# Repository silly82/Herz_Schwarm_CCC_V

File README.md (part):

# ❤️ CCC Heart Swarm Badge (Herz-Schwarm)

Synchronized ESP-NOW Heart Badges for the CCC Camp & Congress.
*Synchronisierte ESP-NOW Herz-Badges für das CCC Camp & den Congress.*

---

## Deutsch

### Was ist das?
Ein Schwarm von 8x8 LED Herz-Badges auf Basis der **Waveshare ESP32-S3-Matrix**. Die Badges kommunizieren über **ESP-NOW**, synchronisieren ihren Takt, reagieren auf die Nähe anderer Geräte (RSSI) und enthalten interaktive Easter Eggs.

### Funktionen
- **Herzschlag-Sync:** Alle Badges schlagen im exakt gleichen Rhythmus.
- **Näherungseffekt:** Je näher dir ein anderes Badge kommt, desto heller leuchtet dein Herz. Ab Badge-FW 1.6.0 zählt dafür das **nächste** Badge (stärkstes Signal), nicht mehr der Durchschnitt über alle; das Tempo hängt nicht mehr an der Nähe, damit alle im gleichen Takt bleiben. Ferngesteuerte Effekte leuchten auf allen Badges gleich hell (feste Helligkeit, `FX_BRIGHT`).
- **Primzahlen-Osterei:** Wenn die **Gesamtzahl im Schwarm** eine Primzahl ist — also **sichtbare andere Badges plus dein eigenes** (z. B. du + 12 andere = 13; nur unter 17, ab dort greift die Singularität) — pulsiert das Herz stärker und es gibt weisse Glitzer-Pixel.
- **Die Singularität (≥17 Geräte):** Sobald **mindestens 17 Geräte insgesamt** da sind (du + 16 sichtbare Peers), schaltet die Animation auf den **Regenbogen-Modus** um (nicht nur bei exakt 17).
- **Der Morse-Virus:** Morsese ein **«C»** (`- . - .`) über die BOOT-Taste, um einen weissen Blitz-Virus durch den gesamten Schwarm zu jagen. Ab Badge-FW 1.6.0 endet der Morse-Virus auf jedem Badge nach **3 s** von selbst (am Badge gibt es keine Stopp-Geste); nur der von Basisstation/App gestartete Virus läuft endlos bis zum Stopp.
- **Die Welle (Basisstation):** Eine Welle breitet sich von der Basisstation aus: Badges in der Nähe leuchten zuerst, weiter entfernte später. Ein Durchlauf dauert ~4 s und wiederholt sich ab Badge-FW 1.4.1 **endlos** (Zyklus alle 4000 ms) — beendet wird die Welle erst per **manuellem Stopp** (Modus `10`, oder `12` für alle Effekte): Toggle im Web-UI, MQTT-Payload `10` oder Nerves-Dashboard; Badges leiten den Stopp begrenzt weiter, so erreicht er auch Geräte außerhalb der Basis-Reichweite. Ältere Badges verstehen den Stopp nicht und laufen wie bisher nach ~4 s aus. Ab Badge-FW 1.4.0: Wer die Basis direkt hört, zündet nach deren Signal (−45 dBm → sofort, −95 dBm → 2 s); alle anderen nach dem Badge, von dem sie die Welle haben, plus 150–750 ms je nach Signal zu ihm. Jedes Badge rechnet dabei auf den gemeinsamen Wellenstart zurück und übernimmt den kürzesten bekannten Weg — die Welle läuft so auch zu Badges, die die Basis gar nicht hören.
- **Fernauslösung (Basisstation):** Kompatibles `SyncPacket` mit `mode` **1** (Virus), **2** (Regenbogen / Singularity-Optik), **3** (Primzahl-Party), **4** (Welle / RSSI-Ripple, 4-s-Zyklus), **5** (Beat-Puls ~150 ms), **6** (RSSI-Zonen-Farben), **7** (Ambient-Farbe), **8** (Strobe), **9** (Badge finden — nur das Badge mit der Ziel-MAC blinkt grün), **10** (Welle stoppen — beendet die laufende Welle, ab Badge-FW 1.4.1), **11** (Tap-Meldung — `virusID` = Tap-Zählerstand), **12** (Alle stoppen — global, `virusID` = Kennung des Stopps), **13** (Funk-Update auslösen — nur App + Bridge, ab Badge-FW 1.7.0). Ab Badge-FW **1.5.0** laufen alle visuellen Effekte **endlos**, bis man sie stoppt oder ein neu gestarteter visueller Effekt sie ersetzt („letzter Effekt gewinnt" — Beat und Identify bleiben dabei erhalten). Die früheren festen Fenster (Virus 3 s, Regenbogen 15 s, Primzahl 12 s, Zonen 5 s, Ambient 30 s, Strobe 2 s) sind nur noch **nominale Zykluslängen**, nach denen der Effekt sich wiederholt. Ausnahmen: **Beat** bleibt ein 150-ms-Puls pro Paket, **Identify** (Modus 9) bleibt 10 s. Neue `virusID` pro Effekt verhindert Doppel-Trigger; während eines Effekts wird der passende `mode` weitergesendet (Kettenreaktion im Schwarm).
- **Tap-Counter (BOOT-Taste, ab Badge-FW 1.5.0):** Kurze Drücke auf die BOOT-Taste (**≤ 250 ms** — dieselben Ereignisse, die in der Morse-Eingabe ein Punkt sind; Morse unverändert) werden gezählt und als Modus `11` gemeldet (`virusID` = Zählerstand, monoton; 3× im 60-ms-Abstand plus Nachsendung nach 1,2 s, einmal beim Start). Andere Badges leiten fremde Tap-Pakete begrenzt weiter (**23 Byte** mit angehängter Ursprungs-MAC) und merken sich je MAC den höchsten Stand (Dedup). Der Zählerstand wird gedrosselt in NVS gespeichert (Namespace `hstap`, max. 1 Schreibvorgang/30 s). In der Nerves-App endet die Kette als **Tap-Counter-Karte** (Gesamtsumme und je Badge, Reset mit Rückfrage — Reset setzt nur die Anzeige auf 0, die Badge-Zähler laufen weiter).
- **Alle stoppen (Modus `12`, ab Badge-FW 1.5.0):** Globaler Stopp. Ab Badge-FW 1.6.0 / Basisstation 0.4.2 / Bridge 0.4.2 / App 0.2.2 trägt jeder Stopp eine eigene Kennung im `virusID`-Feld und wirkt je Badge genau einmal — ein verspätetes Echo schaltet so keinen Effekt mehr ab, der nach dem Stopp gestartet wurde (`virusID = 0` von älteren Sendern wird weiter verstanden, dann ohne diesen Schutz). Badges deaktivieren alle Effekt-Slots außer Identify und leiten den Stopp begrenzt weiter (max. 3 Sendungen, ~60 ms Abstand, dann 1000 ms Sperre — gleiches Muster wie der Wellen-Stopp). Erreichbar über Dashboard-Knopf „Alle Effekte auf den Badges stoppen", Basisstation-Knopf „⏹ Alle stoppen", `POST /api/effect?m=12` oder MQTT-Payload `12`.
- **Bewegungssensor (ab Badge-FW 1.8.0):** Schütteln lässt das Herz 1,5 s mit weißen Funken flattern. Optional: „Herz immer aufrecht" und Abdunkeln in Ruhe (beides standardmäßig aus). Am Gerät noch nicht getestet — siehe *Bewegungssensor*.
- **Funk-Update (ab Badge-FW 1.7.0):** Badges laden eine neue Firmware selbst per WLAN, ausgelöst über den Schwarm-Funk von der App-Seite `/badge-update` (Modus `13`, mit Schlüssel abgesichert). Nur in Builds mit `ota_secret.h`; am Gerät noch nicht getestet — siehe *Funk-Update der Badges*.
- **Nerves-Controller (Raspberry Pi):** Optionale Elixir/Nerves-App (`herz_schwarm_nerves/`) steuert den Schwarm über einen USB-ESP32-Bridge (ESP-NOW). LiveView Web-UI für Effekt-Steuerung, Beat-Tap-Tempo, Ambient-Farbwahl. Koexistiert mit der Basisstation auf Kanal 13. **Dev-Start auf Mac** (ohne Nerves-Build): siehe `herz_schwarm_nerves/MAC_SETUP.md`. Ab App 0.2.0 / Bridge 0.3.0 steuert die Seite **`/bridge-update`** die Bridge-Firmware per **UART-OTA** über das bestehende USB-Kabel (kein WLAN, kein `esptool`) — die Bridge braucht dafür einmalig einen USB-Flash mit dem neuen Partition-Schema `min_spiffs`; Details in Punkt 12 der nummerierten Doku. Ab App 0.2.0 / Bridge 0.4.0 zusätzlich im Dashboard: **Tap-Counter-Karte** (Modus `11`) und Knopf „Alle Effekte auf den Badges stoppen" (Modus `12`); BPM-Slider und Farbwähler wurden in Formulare gesetzt (vorher kamen Tempo- und Farbänderungen nie an) und das Verschieben des Tempo-Sliders startet den Beat nicht mehr. Ab App 0.3.0 / Bridge 0.5.0 löst die Seite **`/badge-update`** das Funk-Update der Badges aus. Betrieb auch direkt auf **Raspberry Pi OS** (systemd-Dienst, ohne Nerves-Firmware) — siehe *Betrieb auf dem Raspberry Pi*.

### Spezifische Hardware-Hinweise (Waveshare ESP32-S3-Matrix)
- **Pinout:** Die interne Matrix ist fest an **GPIO 14** verdrahtet. Die BOOT-Taste liegt auf **GPIO 0**.
- **Farben:** Die Matrix der Waveshare-Boards ist **RGB** verdrahtet (am Gerät verifiziert — mit `BGR` waren Rot und Blau vertauscht). Die Firmware initialisiert entsprechend `FastLED.addLeds<WS2812B, LED_PIN, RGB>`.
- **Sicherheit:** Da die Rückseite des Boards offene Kontakte hat, wird dringend empfohlen, diese mit Klebeband (Kapton) zu isolieren oder ein Gehäuse zu verwenden.
- **Eigene Hardware:** `herz_badge/` enthält das KiCad-Projekt für ein akkubetriebenes Badge (Waveshare-Schaltplan nachgezeichnet, Akku-Version platziert, noch nicht geroutet). Siehe `herz_badge/README.md`.

---

## 🇬🇧 English

### What is this?
A swarm of 8x8 LED heart badges based on the **Waveshare ESP32-S3-Matrix**. They communicate via **ESP-NOW**, sync their pulse, react to proximity (RSSI), and feature interactive Easter Eggs.

### Features
- **Heartbeat Sync:** All badges beat at the exact same rhythm.
- **Proximity Awareness:** The closer another badge gets, the brighter your heart glows. From badge FW 1.6.0 this follows the **nearest** badge (strongest signal) instead of the average over all peers; tempo no longer depends on proximity, so everyone stays on the same beat. Remote-triggered effects use a fixed brightness (`FX_BRIGHT`) and look the same on every badge.
- **Prime Number Easter Egg:** When the **total swarm size** is prime — **other visible badges plus your own** (e.g. you + 12 others = 13; only below 17, where the singularity takes over) — the heart pulses more strongly with occasional white sparkles.
- **The Singularity (≥17 devices):** When **at least 17 devices** are present in total (you + 16 visible peers), the animation switches to **rainbow mode** (not only at exactly 17).
- **The Morse Virus:** Morse a **"C"** (`- . - .`) using the BOOT button to trigger a white flash "virus" across the entire swarm. From badge FW 1.6.0 the Morse virus ends after **3 s** on every badge (there is no stop gesture on the badge); only a virus started from the base station or the app runs until stopped.
- **The Wave (base station):** A wave ripples outward from the base station: nearby badges light up first, distant ones later. One pass takes ~4 s; from badge FW 1.4.1 the wave **repeats endlessly** (4000 ms cycle) and only ends on a **manual stop** (mode `10`, or `12` to stop all effects): toggle in the web-UI, MQTT payload `10`, or Nerves dashboard — badges relay the stop with limited rebroadcasts, so it also reaches devices outside the base's range. Older badges don't understand the stop and finish after ~4 s as before. From badge FW 1.4.0, badges that hear the base fire by its signal strength (−45 dBm → immediately, −95 dBm → 2 s); others fire after the badge they got the wave from, plus 150–750 ms by signal to it. Every badge aligns to the shared wave start and keeps the shortest known path, so the wave also reaches badges out of the base's range.
- **Remote trigger (base station):** Compatible `SyncPacket` with `mode` **1** (virus), **2** (rainbow / singularity look), **3** (prime-party look), **4** (wave / RSSI ripple, 4 s cycle), **5** (beat pulse ~150 ms), **6** (RSSI zone colors), **7** (ambient color), **8** (strobe), **9** (find badge — only the badge with the target MAC blinks green), **10** (stop the wave — ends the running wave, badge FW 1.4.1+), **11** (tap report — `virusID` = tap counter), **12** (stop all — global, `virusID` = id of this stop), **13** (trigger over-the-air update — app + bridge only, badge FW 1.7.0+). From badge FW **1.5.0** all visual effects run **endlessly** until stopped or until a newly started visual effect replaces them ("last effect wins" — beat and identify are kept). The previous fixed windows (virus 3 s, rainbow 15 s, prime 12 s, zones 5 s, ambient 30 s, strobe 2 s) are now only **nominal cycle lengths** after which the effect repeats. Exceptions: **beat** remains a 150 ms pulse per packet, **identify** (mode 9) stays at 10 s. A fresh `virusID` per effect avoids re-triggering; while active, badges forward the same `mode` for swarm propagation.
- **Tap counter (BOOT button, badge FW 1.5.0+):** Short BOOT presses (**≤ 250 ms** — the same events that count as a dot in morse input; morse itself is unchanged) are counted and reported as mode `11` (`virusID` = counter, monotonic; sent 3× at 60 ms spacing plus a re-send after 1.2 s, and once at boot). Other badges relay foreign tap packets with limited rebroadcast (**23 bytes** with the origin MAC appended) and keep the highest value per MAC (dedup). The counter is persisted to NVS with throttling (namespace `hstap`, max. 1 write/30 s). In the Nerves app the chain ends on a **Tap-Counter card** (total and per badge, reset with confirmation — reset only zeroes the display, badge counters keep running).
- **Stop all (mode `12`, badge FW 1.5.0+):** Global stop. From badge FW 1.6.0 / base station 0.4.2 / bridge 0.4.2 / app 0.2.2 every stop carries its own id in `virusID` and takes effect exactly once per badge, so a late echo can no longer switch off an effect started after the stop (`virusID = 0` from older senders is still understood, without that protection). Badges deactivate all effect slots except identify and relay the stop with limited rebroadcast (max. 3 sends, ~60 ms apart, then a 1000 ms lock — same pattern as the wave stop). Reachable via the dashboard button "Alle Effekte auf den Badges stoppen", the base station button "⏹ Alle stoppen", `POST /api/effect?m=12`, or MQTT payload `12`.
- **Motion sensor (badge FW 1.8.0+):** Shaking the badge makes the heart flutter with white sparks for 1.5 s. Optional: "heart always upright" and dimming at rest (both off by default). Not yet tested on hardware — see *Bewegungssensor* (German).
- **Over-the-air update (badge FW 1.7.0+):** Badges download new firmware over Wi-Fi themselves, triggered through the swarm radio from the app page `/badge-update` (mode `13`, protected by a shared key). Only in builds with `ota_secret.h`; not yet tested on hardware — see *Funk-Update der Badges* (German).
- **Nerves Controller (Raspberry Pi):** Optional Elixir/Nerves app (`herz_schwarm_nerves/`) controls the swarm via a USB ESP32 bridge (ESP-NOW). LiveView web-UI for effect control, beat tap-tempo, ambient color picker. Coexists with the base station on channel 13. From app 0.2.0 / bridge 0.3.0 the **`/bridge-update`** page pushes new bridge firmware via **UART-OTA** over the existing USB cable (no Wi-Fi, no `esptool`) — existing bridge devices first need one USB flash with the new `min_spiffs` partition scheme. **Security note:** the `/bridge-update` page has **no login** — anyone who can reach the app on the network can upload and flash bridge firmware. Run the app only in a trusted network or restrict access at the network level (firewall/VPN/LAN segment); there is deliberately no login yet, unlike the base station's OTA, which uses HTTP Basic Auth. From app 0.2.0 / bridge 0.4.0 the dashboard also shows a **Tap-Counter card** (mode `11`) and an "Alle Effekte auf den Badges stoppen" button (mode `12`); the BPM slider and color picker now sit inside forms (`phx-change` does not fire on standalone inputs outside a form, so tempo and color changes never arrived), and moving the tempo slider no longer starts the beat (start only via "Start"). From app 0.3.0 / bridge 0.5.0 the **`/badge-update`** page triggers the over-the-air update of the badges (also without login; a trigger additionally needs the shared key `BADGE_OTA_KEY` on the server). The app also serves the diagnosis page **`/diagnose`** (monitoring: counters, bridge state, log panel, badge metrics). The app currently runs on plain **Raspberry Pi OS (Debian 13, aarch64)** as systemd service `herz-schwarm` on port 4000 — no Nerves firmware; see `herz_schwarm_nerves/MAC_SETUP.md`.

### Specific Hardware Notes (Waveshare ESP32-S3-Matrix)
- **Pinout:** Internal matrix is wired to **GPIO 14**. BOOT button is on **GPIO 0**.
- **Color Order:** The matrix is wired **RGB** (verified on device — with `BGR`, red and blue were swapped). The firmware initializes `FastLED.addLeds<WS2812B, LED_PIN, RGB>`.
- **Safety:** As the back of the board has exposed contacts, it is highly recommended to insulate it with tape (Kapton) or use a 3D-printed case.
- **Own hardware:** `herz_badge/` holds the KiCad project for a battery-powered badge (the Waveshare schematic redrawn, the battery version placed, not yet routed). See `herz_badge/README.md`.

### Build, flash & serial monitor (Arduino CLI)
- **FQBN:** `esp32:esp32:esp32s3` — sketch folder = repository root (`Herz_Schwarm_CCC_V.ino`). Port: `arduino-cli board list`.
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
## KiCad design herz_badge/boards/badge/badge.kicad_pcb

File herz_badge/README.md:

# Herz-Schwarm Badge

Status (2026-10-17): reference board (Waveshare ESP32-S3-Matrix) redrawn and checked against the vendor's netlist.
Battery badge: datasheets summarised (`docs/datasheets/`), power path simulated (`sim/`), parts revised after both,
placed on 30 × 34 mm, 4 layers, not routed; JLC order files for a quote; parts $8.91 per board at 100 (BOM.md).

A battery-powered badge that runs the Herz-Schwarm firmware (`../Herz_Schwarm_CCC_V.ino`) unchanged, slightly larger
than the Waveshare ESP32-S3-Matrix the badges use today. `reference` is the Waveshare board as drawn by its maker;
`badge` is the battery version.

| Folder | Contents |
| --- | --- |
| `boards/badge/` | the battery badge: schematic (`power`, `mcu`, `leds`) and placed board, both generated |
| `boards/reference/` | the Waveshare board in KiCad: root sheet plus `power`, `mcu`, `leds`; schematic only, generated |
| `design/reference-netlist.json` | the vendor netlist, read from the bookmarks of Waveshare's schematic PDF |
| `lib/` | project symbols (QMI8658A), footprints (Walsin RFANT3216120A5T antenna, LED without silk) |
| `scripts/` | `sch_badge.py`, `place_badge.py`, `bom_cost.py`, `fetch_datasheets.py`; `vendor_netlist.py`, `sch_reference.py`, `check_reference.py`; `builder.py` is the pcb-kit glue |
| `sim/` | ngspice power-path simulations (runtime, charging, white-flash sag, USB unplug) and their results |
| `docs/previews/` | `badge/` by `pcbkit previews` (+ `ratsnest.png` by `pcbkit place-score`); `reference/schematic.pdf` by kicad-cli |
| `docs/datasheets/` | datasheet summaries with page references ([index](docs/datasheets/README.md)); the PDFs are fetched, not kept |

Regenerate the badge and its quote files:

```bash
python3 scripts/sch_badge.py && pcbkit erc boards/badge/badge.kicad_sch   # both scripts refuse to run while KiCad has the board open
python3 scripts/place_badge.py        # rebuilds the unrouted board; prints courtyard overlaps
pcbkit drc boards/badge/badge.kicad_pcb           # 0 errors expected; unconnected nets until routed
pcbkit previews boards/badge/badge.kicad_pcb docs/previews/badge
pcbkit fab boards/badge/badge.kicad_pcb build/fab/badge
cd boards/badge && bomi import kicad badge.kicad_pro --replace && bomi list --check && cd ../.. && python3 scripts/bom_cost.py boards/badge
python3 scripts/fetch_datasheets.py   # datasheet PDFs into docs/datasheets/
uv run --no-project --with matplotlib python sim/runtime.py   # and charge.py, flash_sag.py, unplug.py
```

Regenerate and check the reference:

```bash
python3 scripts/sch_reference.py      # writes boards/reference/*.kicad_sch through konnect
python3 scripts/check_reference.py    # KiCad netlist vs design/reference-netlist.json, pin for pin
pcbkit erc boards/reference/reference.kicad_sch
kicad-cli sch export pdf -o docs/previews/reference/schematic.pdf boards/reference/reference.kicad_sch
cd boards/reference && bomi import kicad reference.kicad_pro && bomi status
```

See [DESIGN.md](DESIGN.md), [LAYOUT.md](LAYOUT.md), [PRODUCTION.md](PRODUCTION.md), [BOM.md](BOM.md).

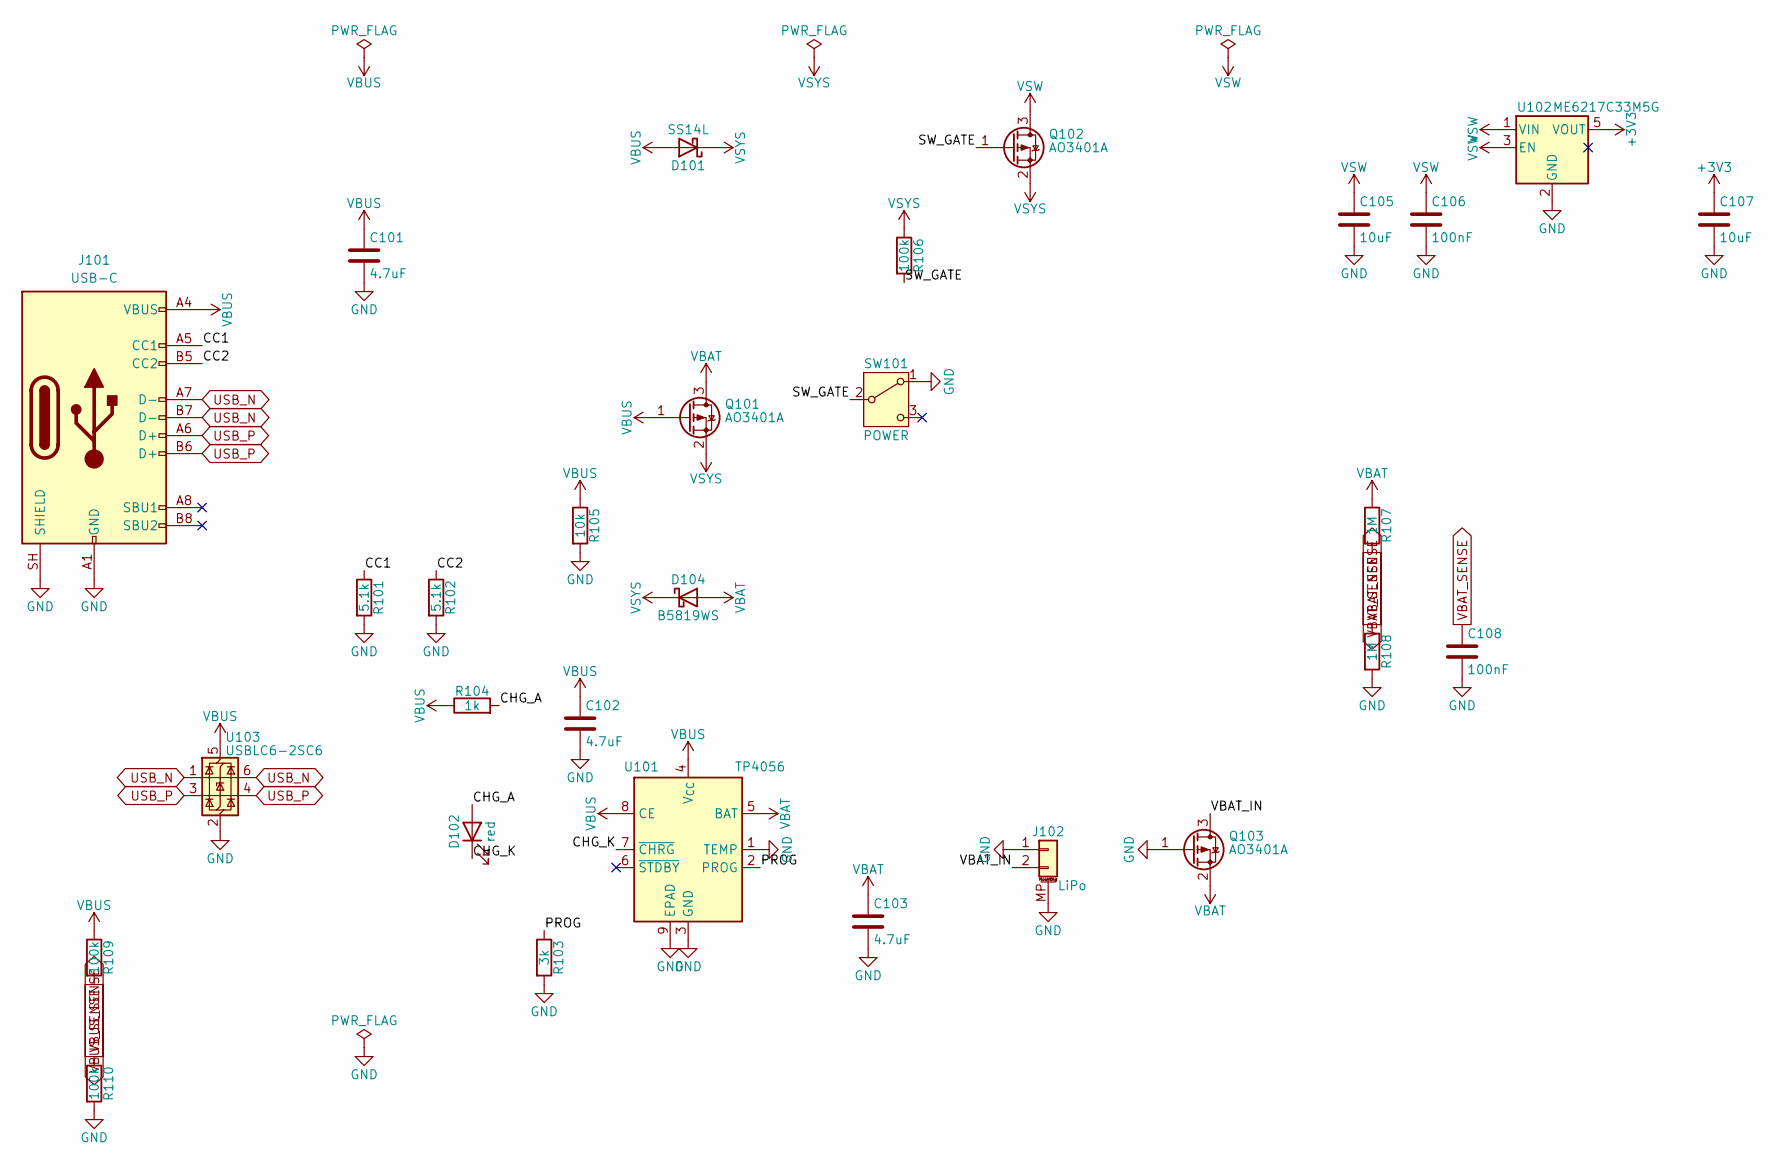
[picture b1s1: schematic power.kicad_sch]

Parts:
C101, C102, C103: 4.7uF; C_0402_1005Metric; LCSC C23733
C105, C107: 10uF; C_0603_1608Metric; LCSC C19702
C106, C108: 100nF; C_0402_1005Metric; LCSC C1525
D101: SS14L; D_SOD-123F; LCSC C190475
D102: red; LED_0603_1608Metric; LCSC C2286
D104: B5819WS; D_SOD-323; LCSC C64886
J101: USB-C; USB_C_Receptacle_HRO_TYPE-C-31-M-12; LCSC C165948
J102: LiPo; JST_PH_S2B-PH-SM4-TB_1x02-1MP_P2.00mm_Horizontal; LCSC C295747
Q101, Q102, Q103: AO3401A; SOT-23; LCSC C15127
R101, R102: 5.1k; R_0402_1005Metric; LCSC C25905
R103: 3k; R_0603_1608Metric; LCSC C4211
R104: 1k; R_0402_1005Metric; LCSC C11702
R105: 10k; R_0402_1005Metric; LCSC C25744
R106, R109, R110: 100k; R_0402_1005Metric; LCSC C25741
R107, R108: 1M; R_0402_1005Metric; LCSC C26083
SW101: POWER; SW_SPDT_Shouhan_MSK12C02; LCSC C431540
U101: TP4056; SOIC-8-1EP_3.9x4.9mm_P1.27mm_EP2.41x3.3mm; LCSC C725790
U102: ME6217C33M5G; SOT-23-5; LCSC C427602
U103: USBLC6-2SC6; SOT-23-6; LCSC C7519

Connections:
+3V3: C107.1, U102.5 (VOUT); also elsewhere on the board
/Power/CC1: J101.A5 (CC1), R101.1
/Power/CC2: J101.B5 (CC2), R102.1
/Power/CHG_A: D102.2 (A), R104.2
/Power/CHG_K: D102.1 (K), U101.7 (~CHRG)
/Power/PROG: R103.1, U101.2 (PROG)
/Power/SW_GATE: Q102.1 (G), R106.2, SW101.2 (B)
/Power/VBAT_IN: J102.2, Q103.3 (D)
GND: C101.2, C102.2, C103.2, C105.2, C106.2, C107.2, C108.2, J101.A1 (GND), J101.A12 (GND), J101.B1 (GND), J101.B12 (GND), J101.SH (SHIELD), J102.1, J102.MP (MountPin), Q103.1 (G), R101.2, R102.2, R103.2, R105.2, R108.2, R110.2, SW101.1 (A), U101.1 (TEMP), U101.3 (GND), U101.9 (EPAD), U102.2 (GND), U103.2 (GND); also elsewhere on the board
USB_N: J101.A7 (D-), J101.B7 (D-), U103.1 (I/O1), U103.6 (I/O1); also elsewhere on the board
USB_P: J101.A6 (D+), J101.B6 (D+), U103.3 (I/O2), U103.4 (I/O2); also elsewhere on the board
VBAT: C103.1, D104.2 (A), Q101.3 (D), Q103.2 (S), R107.1, U101.5 (BAT)
VBAT_SENSE: C108.1, R107.2, R108.1; also elsewhere on the board
VBUS: C101.1, C102.1, D101.2 (A), J101.A4 (VBUS), J101.A9 (VBUS), J101.B4 (VBUS), J101.B9 (VBUS), Q101.1 (G), R104.1, R105.1, R109.1, U101.4 (V_{CC}), U101.8 (CE), U103.5 (VBUS)
VBUS_SENSE: R109.2, R110.1; also elsewhere on the board
VSW: C105.1, C106.1, Q102.3 (D), U102.1 (VIN), U102.3 (EN); also elsewhere on the board
VSYS: D101.1 (K), D104.1 (K), Q101.2 (S), Q102.2 (S), R106.1

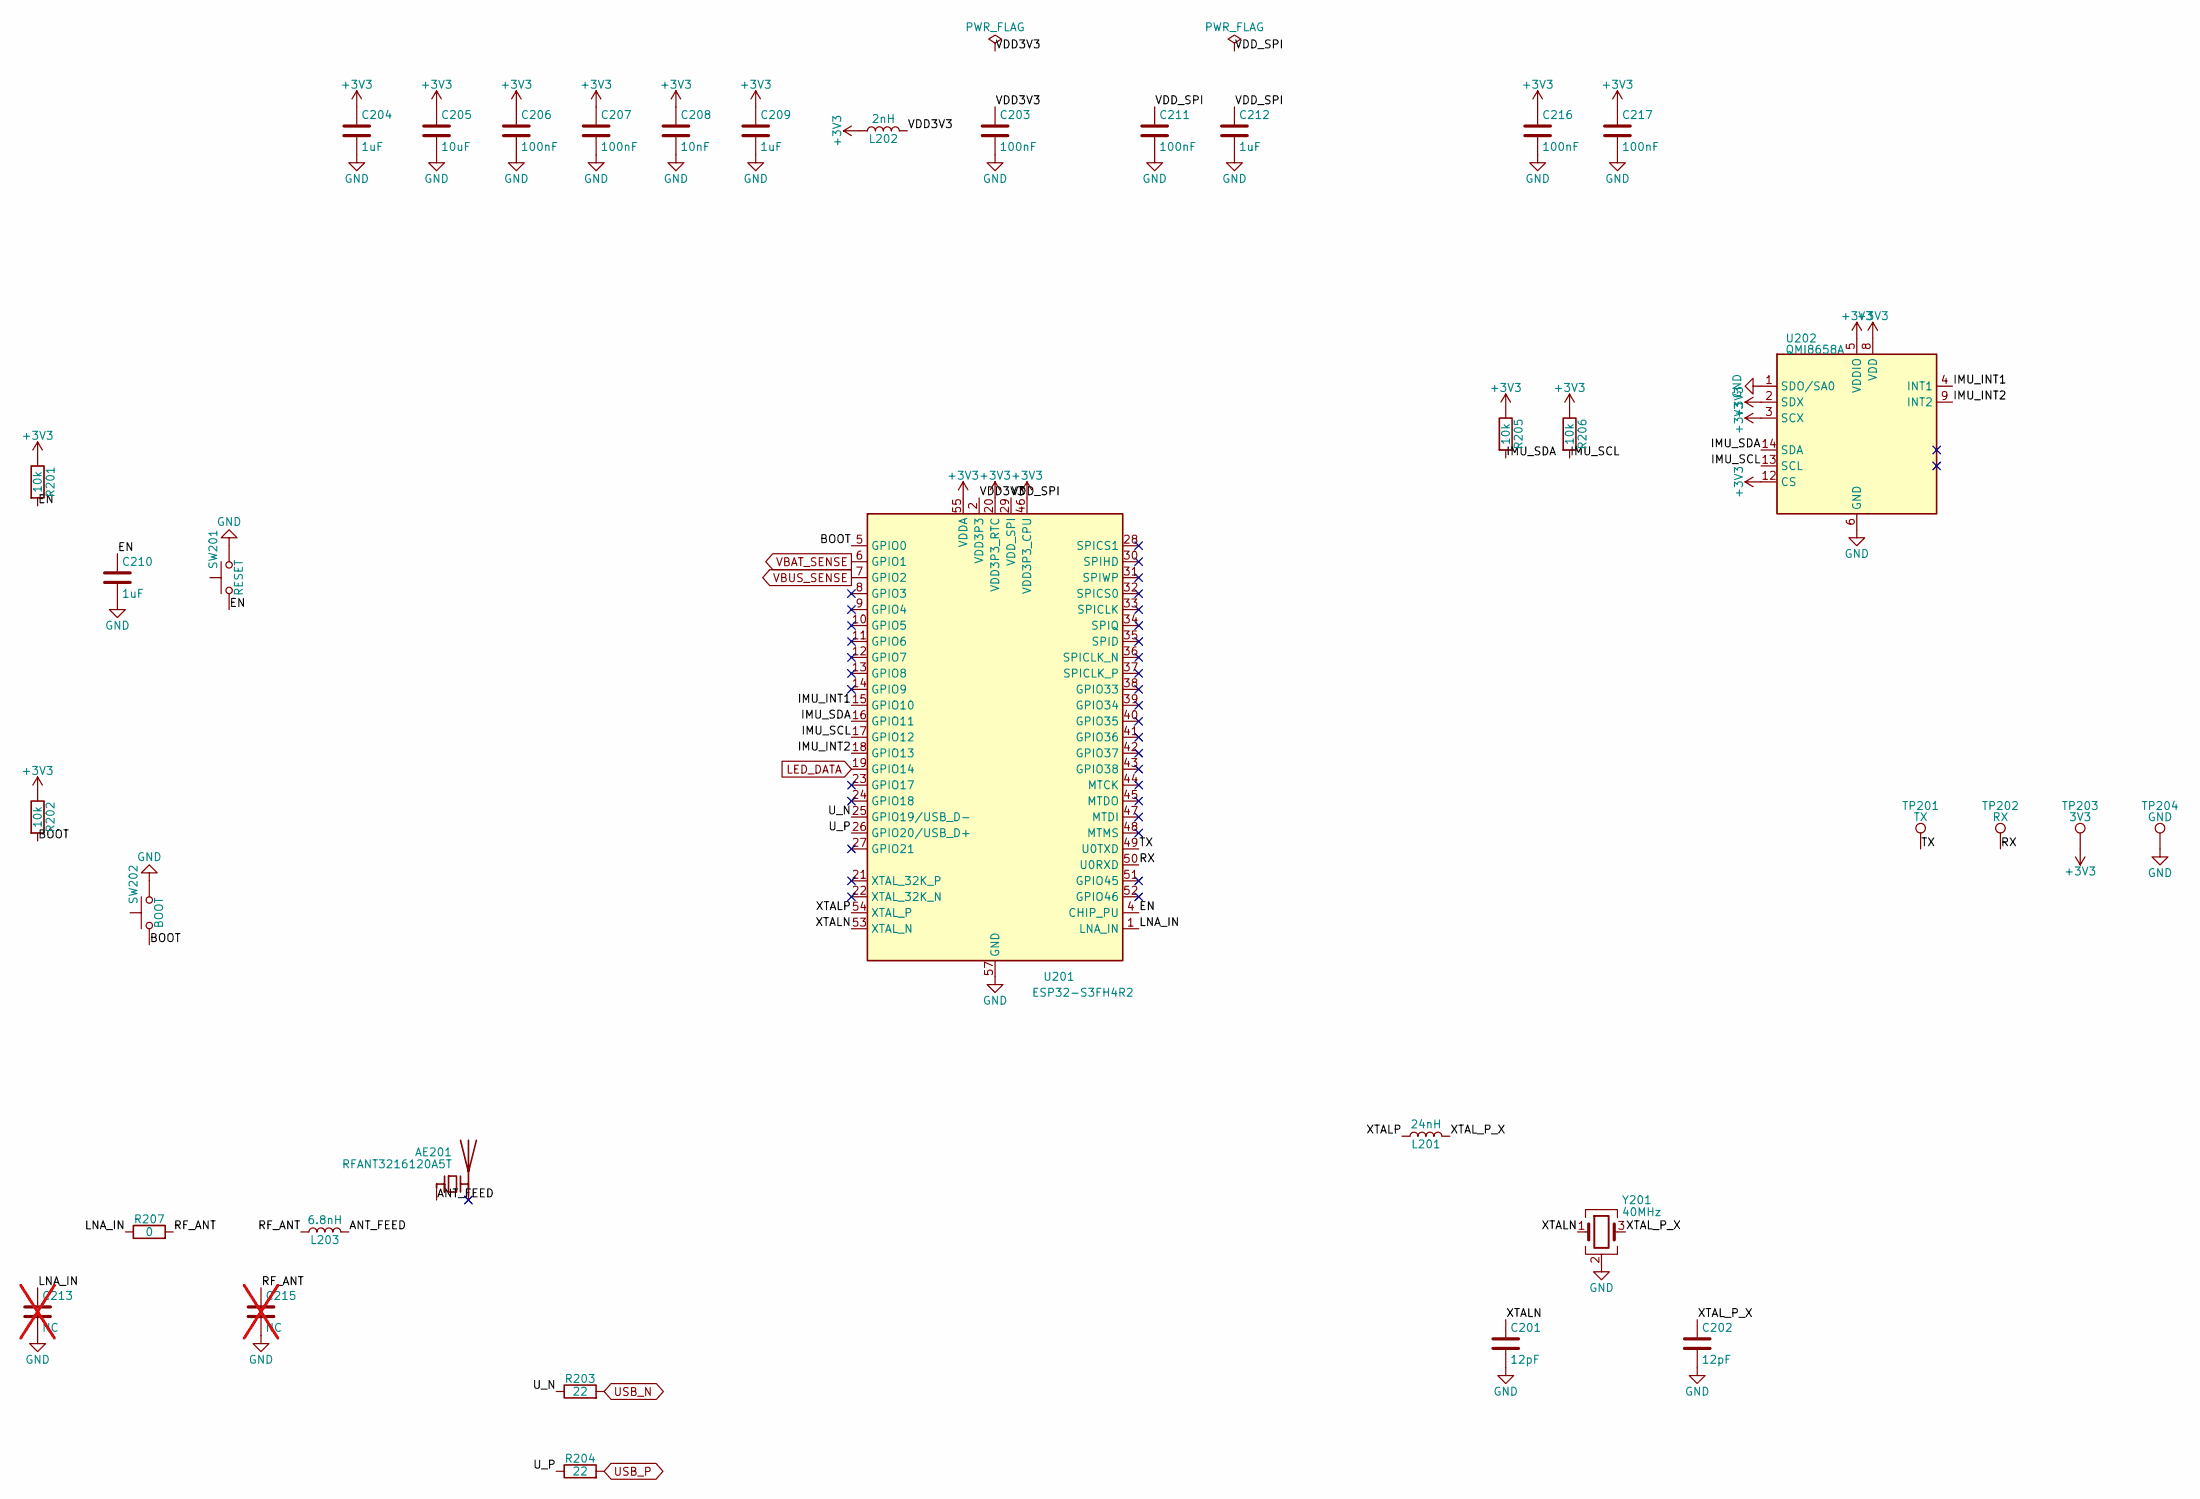
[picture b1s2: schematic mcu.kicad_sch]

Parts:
AE201: RFANT3216120A5T; ANT_Walsin_RFANT3216120A5T; LCSC C127629
C201, C202: 12pF; C_0402_1005Metric; LCSC C1547
C203, C206, C207, C211, C216, C217: 100nF; C_0402_1005Metric; LCSC C1525
C204, C209, C210, C212: 1uF; C_0402_1005Metric; LCSC C52923
C205: 10uF; C_0603_1608Metric; LCSC C19702
C208: 10nF; C_0402_1005Metric; LCSC C15195
C213, C215: NC; C_0402_1005Metric; not fitted
L201: 24nH; L_0402_1005Metric; LCSC C74301
L202: 2nH; L_0402_1005Metric; LCSC C76769
L203: 6.8nH; L_0402_1005Metric; LCSC C77110
R201, R202, R205, R206: 10k; R_0402_1005Metric; LCSC C25744
R203, R204: 22; R_0402_1005Metric; LCSC C25092
R207: 0; R_0402_1005Metric; LCSC C17168
SW201: RESET; SW_SPST_TS-1088-xR020; LCSC C455280
SW202: BOOT; SW_SPST_TS-1088-xR020; LCSC C455280
TP201: TX; TestPoint_Pad_D1.0mm
TP202: RX; TestPoint_Pad_D1.0mm
TP203: 3V3; TestPoint_Pad_D1.0mm
TP204: GND; TestPoint_Pad_D1.0mm
U201: ESP32-S3FH4R2; QFN-56-1EP_7x7mm_P0.4mm_EP4x4mm; LCSC C3013940
U202: QMI8658A; LGA-14_3x2.5mm_P0.5mm_LayoutBorder3x4y; LCSC C3021082
Y201: 40MHz; Crystal_SMD_3225-4Pin_3.2x2.5mm; LCSC C426988

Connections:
+3V3: C204.1, C205.1, C206.1, C207.1, C208.1, C209.1, C216.1, C217.1, L202.1, R201.1, R202.1, R205.1, R206.1, TP203.1, U201.20 (VDD3P3_RTC), U201.46 (VDD3P3_CPU), U201.55 (VDDA), U201.56 (VDDA), U202.2 (SDX), U202.3 (SCX), U202.5 (VDDIO), U202.8 (VDD), U202.12 (CS); also elsewhere on the board
/MCU/ANT_FEED: AE201.1 (FEED), L203.2
/MCU/BOOT: R202.2, SW202.1, U201.5 (GPIO0)
/MCU/EN: C210.1, R201.2, SW201.1, U201.4 (CHIP_PU)
/MCU/IMU_INT1: U201.15 (GPIO10), U202.4 (INT1)
/MCU/IMU_INT2: U201.18 (GPIO13), U202.9 (INT2)
/MCU/IMU_SCL: R206.2, U201.17 (GPIO12), U202.13 (SCL)
/MCU/IMU_SDA: R205.2, U201.16 (GPIO11), U202.14 (SDA)
/MCU/LNA_IN: C213.1, R207.1, U201.1 (LNA_IN)
/MCU/RF_ANT: C215.1, L203.1, R207.2
/MCU/RX: TP202.1, U201.50 (U0RXD)
/MCU/TX: TP201.1, U201.49 (U0TXD)
/MCU/U_N: R203.1, U201.25 (GPIO19/USB_D-)
/MCU/U_P: R204.1, U201.26 (GPIO20/USB_D+)
/MCU/VDD3V3: C203.1, L202.2, U201.2 (VDD3P3), U201.3 (VDD3P3)
/MCU/VDD_SPI: C211.1, C212.1, U201.29 (VDD_SPI)
/MCU/XTALN: C201.1, U201.53 (XTAL_N), Y201.1
/MCU/XTALP: L201.1, U201.54 (XTAL_P)
/MCU/XTAL_P_X: C202.1, L201.2, Y201.3
GND: C201.2, C202.2, C203.2, C204.2, C205.2, C206.2, C207.2, C208.2, C209.2, C210.2, C211.2, C212.2, C213.2, C215.2, C216.2, C217.2, SW201.2, SW202.2, TP204.1, U201.57 (GND), U202.1 (SDO/SA0), U202.6 (GND), U202.7 (GND), Y201.2 (G), Y201.4 (G); also elsewhere on the board
LED_DATA: U201.19 (GPIO14); also elsewhere on the board
USB_N: R203.2; also elsewhere on the board
USB_P: R204.2; also elsewhere on the board
VBAT_SENSE: U201.6 (GPIO1); also elsewhere on the board
VBUS_SENSE: U201.7 (GPIO2); also elsewhere on the board

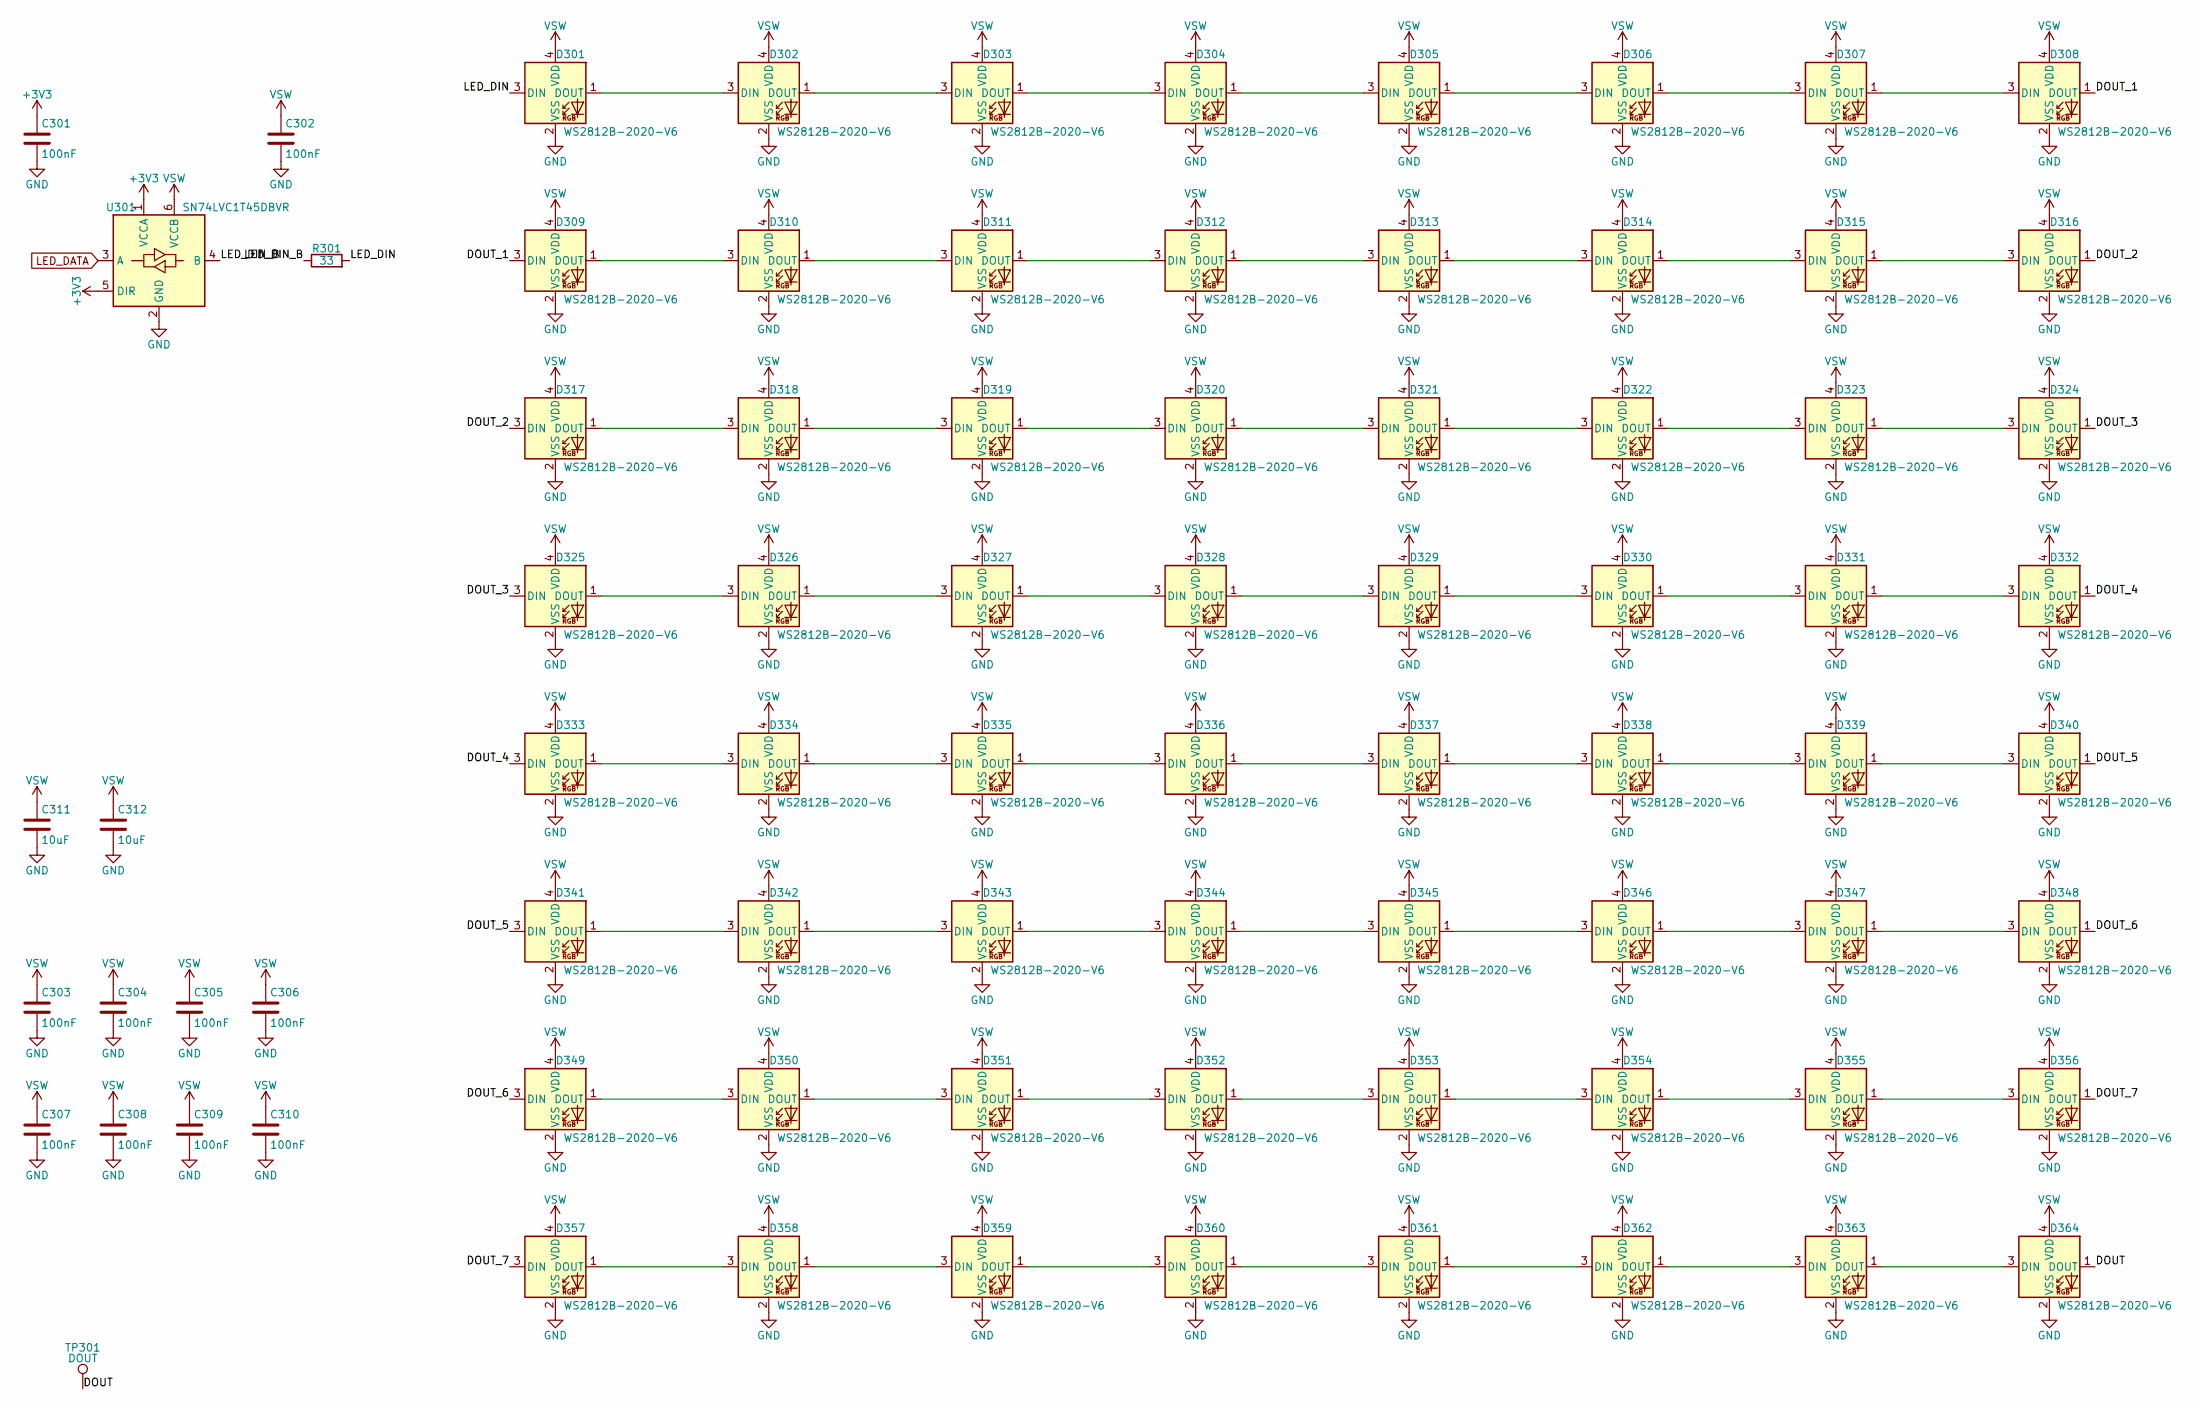
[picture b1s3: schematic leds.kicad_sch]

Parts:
C301, C302, C303, C304, C305, C306, C307, C308, C309, C310: 100nF; C_0402_1005Metric; LCSC C1525
C311, C312: 10uF; C_0603_1608Metric; LCSC C19702
D301, D302, D303, D304, D305, D306, D307, D308, D309, D310, D311, D312, D313, D314, D315, D316, D317, D318, D319, D320, D321, D322, D323, D324, D325, D326, D327, D328, D329, D330, D331, D332, D333, D334, D335, D336, D337, D338, D339, D340, D341, D342, D343, D344, D345, D346, D347, D348, D349, D350, D351, D352, D353, D354, D355, D356, D357, D358, D359, D360, D361, D362, D363, D364: WS2812B-2020-V6; LED_WS2812B-2020_PLCC4_2.0x2.0mm_NoSilk; LCSC C52917434
R301: 33; R_0402_1005Metric; LCSC C25105
TP301: DOUT; TestPoint_Pad_D1.0mm
U301: SN74LVC1T45DBVR; SOT-23-6; LCSC C7843

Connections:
+3V3: C301.1, U301.1 (VCCA), U301.5 (DIR); also elsewhere on the board
/LEDs/DOUT: D364.1 (DOUT), TP301.1
/LEDs/DOUT_1: D308.1 (DOUT), D309.3 (DIN)
/LEDs/DOUT_2: D316.1 (DOUT), D317.3 (DIN)
/LEDs/DOUT_3: D324.1 (DOUT), D325.3 (DIN)
/LEDs/DOUT_4: D332.1 (DOUT), D333.3 (DIN)
/LEDs/DOUT_5: D340.1 (DOUT), D341.3 (DIN)
/LEDs/DOUT_6: D348.1 (DOUT), D349.3 (DIN)
/LEDs/DOUT_7: D356.1 (DOUT), D357.3 (DIN)
/LEDs/LED_DIN: D301.3 (DIN), R301.2
/LEDs/LED_DIN_B: R301.1, U301.4 (B)
GND: C301.2, C302.2, C303.2, C304.2, C305.2, C306.2, C307.2, C308.2, C309.2, C310.2, C311.2, C312.2, D301.2 (VSS), D302.2 (VSS), D303.2 (VSS), D304.2 (VSS), D305.2 (VSS), D306.2 (VSS), D307.2 (VSS), D308.2 (VSS), D309.2 (VSS), D310.2 (VSS), D311.2 (VSS), D312.2 (VSS), D313.2 (VSS), D314.2 (VSS), D315.2 (VSS), D316.2 (VSS), D317.2 (VSS), D318.2 (VSS), D319.2 (VSS), D320.2 (VSS), D321.2 (VSS), D322.2 (VSS), D323.2 (VSS), D324.2 (VSS), D325.2 (VSS), D326.2 (VSS), D327.2 (VSS), D328.2 (VSS), D329.2 (VSS), D330.2 (VSS), D331.2 (VSS), D332.2 (VSS), D333.2 (VSS), D334.2 (VSS), D335.2 (VSS), D336.2 (VSS), D337.2 (VSS), D338.2 (VSS), D339.2 (VSS), D340.2 (VSS), D341.2 (VSS), D342.2 (VSS), D343.2 (VSS), D344.2 (VSS), D345.2 (VSS), D346.2 (VSS), D347.2 (VSS), D348.2 (VSS), D349.2 (VSS), D350.2 (VSS), D351.2 (VSS), D352.2 (VSS), D353.2 (VSS), D354.2 (VSS), D355.2 (VSS), D356.2 (VSS), D357.2 (VSS), D358.2 (VSS), D359.2 (VSS), D360.2 (VSS), D361.2 (VSS), D362.2 (VSS), D363.2 (VSS), D364.2 (VSS), U301.2 (GND); also elsewhere on the board
LED_DATA: U301.3 (A); also elsewhere on the board
unnamed: D301.1 (DOUT), D302.3 (DIN)
unnamed: D302.1 (DOUT), D303.3 (DIN)
unnamed: D303.1 (DOUT), D304.3 (DIN)
unnamed: D304.1 (DOUT), D305.3 (DIN)
unnamed: D305.1 (DOUT), D306.3 (DIN)
unnamed: D306.1 (DOUT), D307.3 (DIN)
unnamed: D307.1 (DOUT), D308.3 (DIN)
unnamed: D309.1 (DOUT), D310.3 (DIN)
unnamed: D310.1 (DOUT), D311.3 (DIN)
unnamed: D311.1 (DOUT), D312.3 (DIN)
unnamed: D312.1 (DOUT), D313.3 (DIN)
unnamed: D313.1 (DOUT), D314.3 (DIN)
unnamed: D314.1 (DOUT), D315.3 (DIN)
unnamed: D315.1 (DOUT), D316.3 (DIN)
unnamed: D317.1 (DOUT), D318.3 (DIN)
unnamed: D318.1 (DOUT), D319.3 (DIN)
unnamed: D319.1 (DOUT), D320.3 (DIN)
unnamed: D320.1 (DOUT), D321.3 (DIN)
unnamed: D321.1 (DOUT), D322.3 (DIN)
unnamed: D322.1 (DOUT), D323.3 (DIN)
unnamed: D323.1 (DOUT), D324.3 (DIN)
unnamed: D325.1 (DOUT), D326.3 (DIN)
unnamed: D326.1 (DOUT), D327.3 (DIN)
unnamed: D327.1 (DOUT), D328.3 (DIN)
unnamed: D328.1 (DOUT), D329.3 (DIN)
unnamed: D329.1 (DOUT), D330.3 (DIN)
unnamed: D330.1 (DOUT), D331.3 (DIN)
unnamed: D331.1 (DOUT), D332.3 (DIN)
unnamed: D333.1 (DOUT), D334.3 (DIN)
unnamed: D334.1 (DOUT), D335.3 (DIN)
unnamed: D335.1 (DOUT), D336.3 (DIN)
unnamed: D336.1 (DOUT), D337.3 (DIN)
unnamed: D337.1 (DOUT), D338.3 (DIN)
unnamed: D338.1 (DOUT), D339.3 (DIN)
unnamed: D339.1 (DOUT), D340.3 (DIN)
unnamed: D341.1 (DOUT), D342.3 (DIN)
unnamed: D342.1 (DOUT), D343.3 (DIN)
unnamed: D343.1 (DOUT), D344.3 (DIN)
unnamed: D344.1 (DOUT), D345.3 (DIN)
unnamed: D345.1 (DOUT), D346.3 (DIN)
unnamed: D346.1 (DOUT), D347.3 (DIN)
unnamed: D347.1 (DOUT), D348.3 (DIN)
unnamed: D349.1 (DOUT), D350.3 (DIN)
unnamed: D350.1 (DOUT), D351.3 (DIN)
unnamed: D351.1 (DOUT), D352.3 (DIN)
unnamed: D352.1 (DOUT), D353.3 (DIN)
unnamed: D353.1 (DOUT), D354.3 (DIN)
unnamed: D354.1 (DOUT), D355.3 (DIN)
unnamed: D355.1 (DOUT), D356.3 (DIN)
unnamed: D357.1 (DOUT), D358.3 (DIN)
unnamed: D358.1 (DOUT), D359.3 (DIN)
unnamed: D359.1 (DOUT), D360.3 (DIN)
unnamed: D360.1 (DOUT), D361.3 (DIN)
unnamed: D361.1 (DOUT), D362.3 (DIN)
unnamed: D362.1 (DOUT), D363.3 (DIN)
unnamed: D363.1 (DOUT), D364.3 (DIN)
VSW: C302.1, C303.1, C304.1, C305.1, C306.1, C307.1, C308.1, C309.1, C310.1, C311.1, C312.1, D301.4 (VDD), D302.4 (VDD), D303.4 (VDD), D304.4 (VDD), D305.4 (VDD), D306.4 (VDD), D307.4 (VDD), D308.4 (VDD), D309.4 (VDD), D310.4 (VDD), D311.4 (VDD), D312.4 (VDD), D313.4 (VDD), D314.4 (VDD), D315.4 (VDD), D316.4 (VDD), D317.4 (VDD), D318.4 (VDD), D319.4 (VDD), D320.4 (VDD), D321.4 (VDD), D322.4 (VDD), D323.4 (VDD), D324.4 (VDD), D325.4 (VDD), D326.4 (VDD), D327.4 (VDD), D328.4 (VDD), D329.4 (VDD), D330.4 (VDD), D331.4 (VDD), D332.4 (VDD), D333.4 (VDD), D334.4 (VDD), D335.4 (VDD), D336.4 (VDD), D337.4 (VDD), D338.4 (VDD), D339.4 (VDD), D340.4 (VDD), D341.4 (VDD), D342.4 (VDD), D343.4 (VDD), D344.4 (VDD), D345.4 (VDD), D346.4 (VDD), D347.4 (VDD), D348.4 (VDD), D349.4 (VDD), D350.4 (VDD), D351.4 (VDD), D352.4 (VDD), D353.4 (VDD), D354.4 (VDD), D355.4 (VDD), D356.4 (VDD), D357.4 (VDD), D358.4 (VDD), D359.4 (VDD), D360.4 (VDD), D361.4 (VDD), D362.4 (VDD), D363.4 (VDD), D364.4 (VDD), U301.6 (VCCB); also elsewhere on the board

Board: 4 copper layers, 144 parts (77 on the bottom side), 102 nets, no tracks yet.

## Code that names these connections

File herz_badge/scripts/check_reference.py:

"""Compare boards/reference/ with the vendor netlist: same parts, same pins on the same nets.

Exports the KiCad netlist, maps each vendor pin to its KiCad pin(s) (the pin maps live in sch_reference.py), and
checks that every vendor net with two or more pins is exactly one KiCad net with exactly those pins, and that every
single-pin vendor net is an unconnected pin in KiCad. Exit 1 on any difference.

    python3 scripts/check_reference.py
"""
import os
import sys

sys.path.insert(0, os.path.dirname(os.path.abspath(__file__)))
import sch_reference as ref  # noqa: E402  (pin maps and the vendor netlist; importing does not build anything)
from pcbkit.checks.netlist import Netlist  # noqa: E402


def kicad_pins(r, vpin):
    m = ref.LED_PINS if r in ref.LEDS else ref.PIN_MAP.get(r, {})
    kp = m.get(vpin, vpin)
    return [(r, k) for k in (kp if isinstance(kp, tuple) else (kp,))]


def main():
    n = Netlist(ref.BOARD + "reference.kicad_sch")
    seen = set()
    for vnet, vpins in ref.VENDOR["nets"].items():
        want = {p for vp in vpins for p in kicad_pins(*vp.split("-", 1))}
        got_nets = {n.pin.get(p) for p in want}
        if len(vpins) == 1:
            (p,) = want
            net = n.pin.get(p)
            n.expect(net is None or net.startswith("unconnected") or len(n.nets[net]) == 1,
                     f"{vnet}: {p[0]}-{p[1]} unconnected (KiCad: {net})")
            continue
        ok = len(got_nets) == 1 and None not in got_nets and n.nets[next(iter(got_nets))] == want
        net = next(iter(got_nets)) if len(got_nets) == 1 else sorted(map(str, got_nets))
        extra = sorted(n.nets[net] - want) if ok is False and isinstance(net, str) and net in n.nets else []
        n.expect(ok, f"{vnet} -> {net} ({len(want)} pins)" + (f" extra {extra}" if extra else ""))
        if isinstance(net, str):
            seen.add(net)
    stray = [k for k, v in n.nets.items() if k not in seen and len(v) > 1]
    n.expect(not stray, f"no KiCad nets beyond the vendor's {stray}")
    # the facts DESIGN.md relies on, by name
    n.expect(n.pin[("U66", "19")] == "IO14" and n.pin[("Q1", "2")] == "IO14", "LED data: GPIO14 -> Q1 source")
    n.expect(n.pin[("Q1", "1")] == "+3V3" and n.pin[("R3", "1")] == "+5V", "Q1 gate on 3V3, drain pulled to 5V")
    n.expect(n.pin[("U66", "5")] == n.pin[("Key2", "1")], "BOOT button on GPIO0")
    n.expect(n.pin[("U66", "16")] == n.pin[("U67", "14")] and n.pin[("U66", "17")] == n.pin[("U67", "13")],
             "IMU SDA on GPIO11, SCL on GPIO12")
    n.expect(n.nodes(n.pin[("U66", "4")]) == 3, "CHIP_PU has only R8 and Key1 (no RC capacitor)")
    n.expect(n.pin.get(("U66", "29"), "unconnected").startswith("unconnected"), "VDD_SPI has no decoupling")
    n.finish()


if __name__ == "__main__":
    main()

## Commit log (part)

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2026-04-16 Debug optional: ENABLE_SERIAL_DEBUG (Standard aus, weniger Ruckeln)
    Made-with: Cursor
2026-04-17 Primzahl-Logik: Gesamtzahl inkl. eigenes Gerät
    - isPrime(totalDevices) mit totalDevices = uniquePeerCount + 1
    - Singularity-Bedingung als uniquePeerCount + 1 >= 17 dokumentiert
    - Cursor-Regel: Arduino CLI für dieses Workspace
    Made-with: Cursor
2026-04-17 README: Primzahl/Singularität (Gesamtzahl), Arduino CLI, BGR wie im Sketch
    Made-with: Cursor
2026-04-17 todo.md: Notizen zu Flash-Optimierung, Merge nach main, Build-Referenz
    Made-with: Cursor
2026-04-18 Firmware 1.0.0: FW_* im Sketch, README Versionierung, build_debug in .gitignore
    Release-Linie 1.0.0 dokumentiert (Git-Historie ohne Tags). Debug-Builds
    zeigen MAJOR.MINOR.DD+debug; Serial-Banner und Status-Zeile bei ENABLE_SERIAL_DEBUG.
    Arduino-CLI-Regel um FW_*-Hinweis ergänzt.
    Made-with: Cursor
2026-04-18 docs: v1.0.0-Tag in README und Sketch-Kommentar vermerken
    Made-with: Cursor
2026-04-18 Basisstation, Remote-Effekte und Dokumentation
    - Badge: ESP-NOW-Modi 2 (Regenbogen) und 3 (Primzahl-Party) per SyncPacket,
    FW_DEBUG_BUILD erhöht; Morse-Virus und lokale Logik unverändert nutzbar.
    - Neu: Sketch Herz_Schwarm_BaseStation mit W5500, Web-UI, /api/peers,
    /api/effect, MQTT über NVS und Web-Formular (Klartext, kein TLS).
    - README um nummerierte Projekt-Doku und mode-Tabelle erweitert; todo.md
    an den Umsetzungsstand angepasst.
2026-06-15 feat: Wave-Effekt (mode 4) — RSSI-basierter Ripple von Basisstation
    - Badge: SYNC_MODE_WAVE, WAVE_DURATION_MS/WAVE_PULSE_MS Defines
    - Badge: OnDataRecv-Handler berechnet waveDelay aus smoothRSSI
    - Badge: Animationsblock nach Prime, vor Singularity (fade-in/hold/fade-out)
    - Badge: Re-Broadcast mit jitter nach waveDelay für Kettenreaktion
    - Base: handleEffect/sendEffectBroadcast akzeptiert mode 4
    - Base: Web-UI Welle-Button, API-Docs auf m=1|2|3|4 aktualisiert
2026-06-15 feat: Nerves-Controller + Badge Modi 5-8 (Beat/Zone/Ambient/Strobe)
    Badge-Firmware (Herz_Schwarm_CCC_V.ino):
    - Neue Modi: Beat (5, weisser Puls 150ms), Zone (6, RSSI-Farben rot/gelb/blau),
    Ambient (7, RGB aus beatCounter, 30s), Strobe (8, weisse Blitze 2s)
    - OnDataRecv-Handler für alle neuen Modi
    - Animationskette: Virus→Rainbow→Prime→Wave→Beat→Zone→Ambient→Strobe→Singularity→Normal
    ESP32-Bridge-Firmware (herz_schwarm_nerves/firmware/esp32_bridge/):
